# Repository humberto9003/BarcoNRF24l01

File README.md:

# Enlace con NRF24L01
Este repositorio contiene el programa para comunicar dos modulos NRF24L01, enviando las señales analogicas de un joystick por radiocomunicacion (2.4GHZ) para controlar un servomotor SG90 y un motor Brushless.

### Requisitos
Para que el código de este repositorio funcione, es necesario contar con lo siguiente:

- Arduino Uno
- IDE de Arduino 1.8 o superior
- Biblioteca RF24
- Servomotor SG90
- Motor Brushless A2212 Kv1400 / Kv2200
- NRF24L01
- Regulador de Voltaje para el NR24L01
- Modulo Joystick de dos ejes.

### Guías

Puedes obtener la biblioteca RF24 desde el siguiente enlace.

https://github.com/nRF24/RF24

Para conocer mas acerca del modulo NRF24L01 puede consultarlo en el siguiente enlace.

http://robots-argentina.com.ar/didactica/arduino-comunicacion-inalambrica-con-nrf24l01/

### Funcionamiento

Para observar el funcionamiento de este proyecto deberás realizar lo siguiente.

1. Configuarar los pines para el motor,servomotor y joystick de tu preferencia en el codigo de RX y Tx.
2. Si no cunetas con un NodeMCU se puede sustituir con otro arduino, solo tendrias que configuarar los pines de igual manera que el codigo de TX.
3. Alimentar el modulo NRF24L01 unicamete y exclusivamente con el regulador de  3.3V
4. En caso de usar el motor alimentarlo de una bateria externa y no del arduino ya que este no proporciona la corriente suficiente.

Podras comunicar dos arduinos por radiocomunicación, para este caso en particular poder manipular un servomor y motor con un Joystick. 

Por: [Humberto Pastor](https://https://github.com/humberto9003)

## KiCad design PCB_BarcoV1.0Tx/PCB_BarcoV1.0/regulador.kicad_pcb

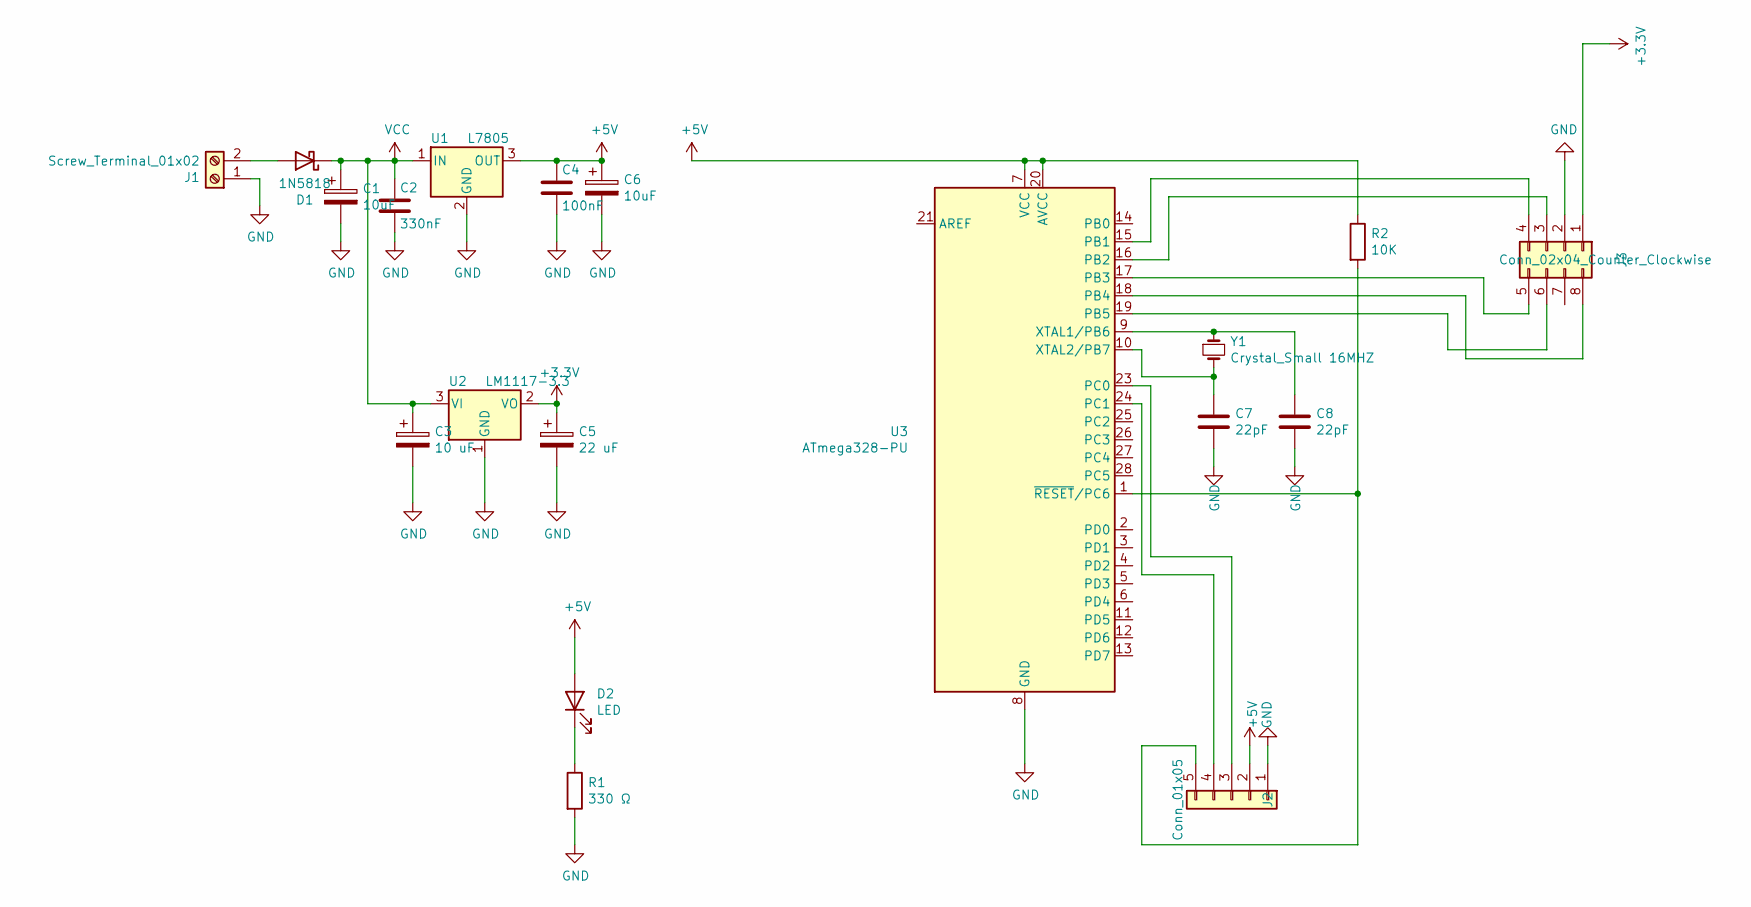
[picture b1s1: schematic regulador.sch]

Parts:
C1, C6: 10uF; CP_Radial_D5.0mm_P2.50mm
C2: 330nF; C_Disc_D6.0mm_W2.5mm_P5.00mm
C3: 10 uF; CP_Radial_D5.0mm_P2.50mm
C4: 100nF; C_Disc_D6.0mm_W2.5mm_P5.00mm
C5: 22 uF; CP_Radial_Tantal_D6.0mm_P2.50mm
C7, C8: 22pF; C_Disc_D5.0mm_W2.5mm_P2.50mm
D1: 1N5818; D_DO-41_SOD81_P10.16mm_Horizontal
D2: LED; LED_D5.0mm
J1: Screw_Terminal_01x02; TerminalBlock_Phoenix_PT-1,5-2-5.0-H_1x02_P5.00mm_Horizontal
J2: Conn_01x05; PinHeader_1x05_P2.54mm_Vertical
J3: Conn_02x04_Counter_Clockwise; PinSocket_2x04_P2.54mm_Vertical
R1: 330 Ω; R_Axial_DIN0207_L6.3mm_D2.5mm_P10.16mm_Horizontal
R2: 10K; R_Axial_DIN0207_L6.3mm_D2.5mm_P10.16mm_Horizontal
U1: L7805; TO-220-3_Horizontal_TabDown
U2: LM1117-3.3; TO-220-3_Horizontal_TabDown
U3: ATmega328-PU; DIP-28_W7.62mm_Socket_LongPads
Y1: Crystal_Small 16MHZ; Crystal_HC49-4H_Vertical

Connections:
+3V3: C5.1, J3.1, U2.2 (VO)
+5V: C4.1, C6.1, D2.2 (A), J2.2, R2.1, U1.3 (OUT), U3.7 (VCC), U3.20 (AVCC)
GND: C1.2, C2.2, C3.2, C4.2, C5.2, C6.2, C7.2, C8.2, J1.1, J2.1, J3.2, R1.2, U1.2 (GND), U2.1 (GND), U3.8 (GND), U3.22 (GND)
unnamed: C7.1, U3.10 (XTAL2/PB7), Y1.2
unnamed: C8.1, U3.9 (XTAL1/PB6), Y1.1
unnamed: D1.2 (A), J1.2
unnamed: D2.1 (K), R1.1
unnamed: J2.3, U3.23 (PC0)
unnamed: J2.4, U3.24 (PC1)
unnamed: J2.5, R2.2, U3.1 (~RESET~/PC6)
unnamed: J3.3, U3.16 (PB2)
unnamed: J3.4, U3.15 (PB1)
unnamed: J3.5, U3.17 (PB3)
unnamed: J3.6, U3.19 (PB5)
unnamed: J3.8, U3.18 (PB4)
VCC: C1.1, C2.1, C3.1, D1.1 (K), U1.1 (IN), U2.3 (VI)

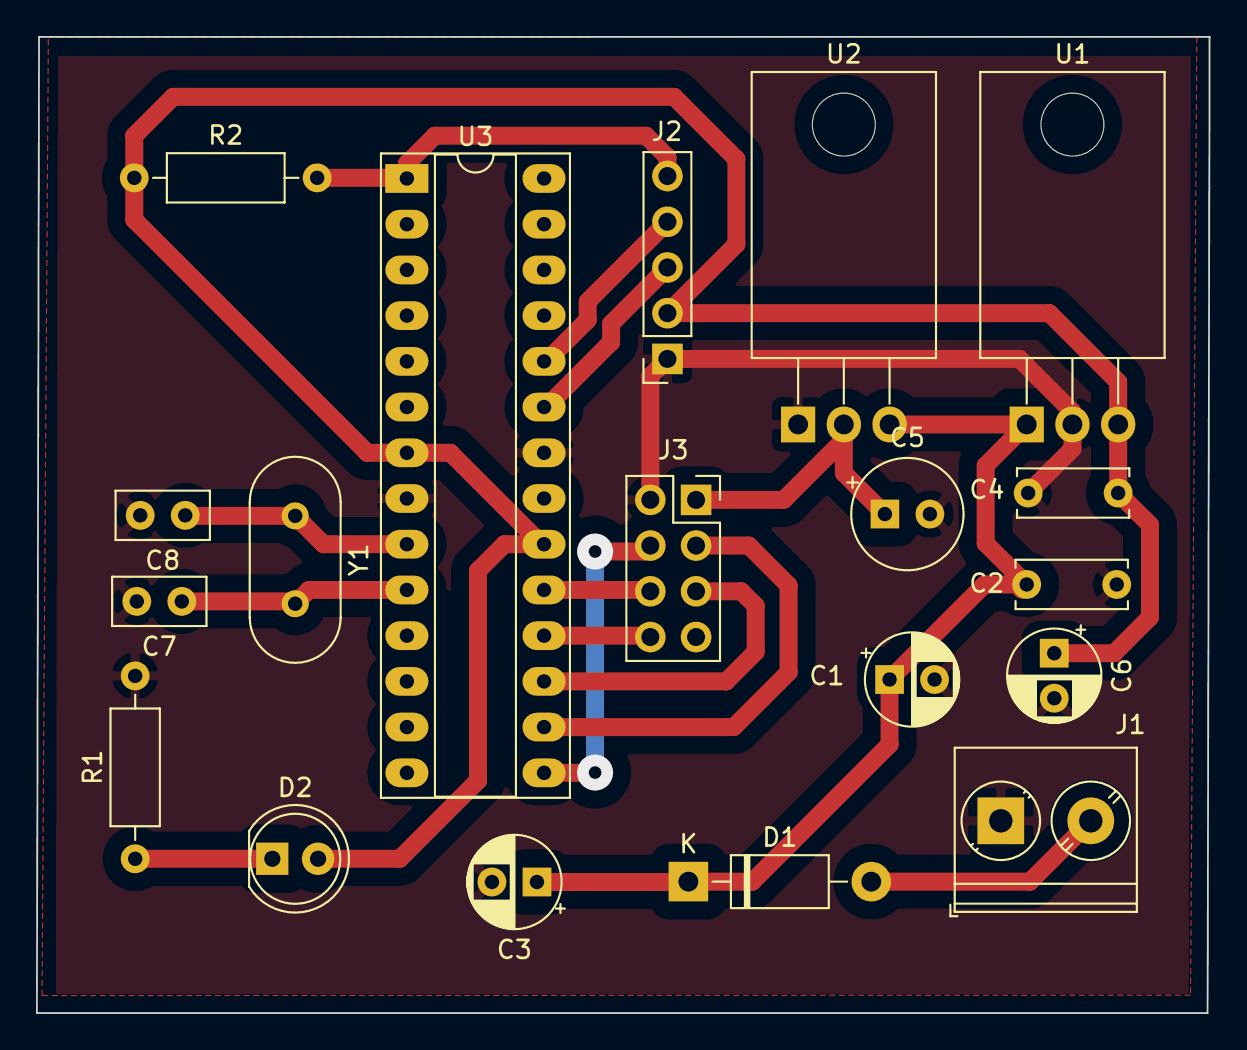
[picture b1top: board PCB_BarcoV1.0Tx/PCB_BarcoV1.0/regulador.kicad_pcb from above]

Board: 2 copper layers, 65.2 x 54.2 mm, 19 parts (0 on the bottom side), 16 nets.

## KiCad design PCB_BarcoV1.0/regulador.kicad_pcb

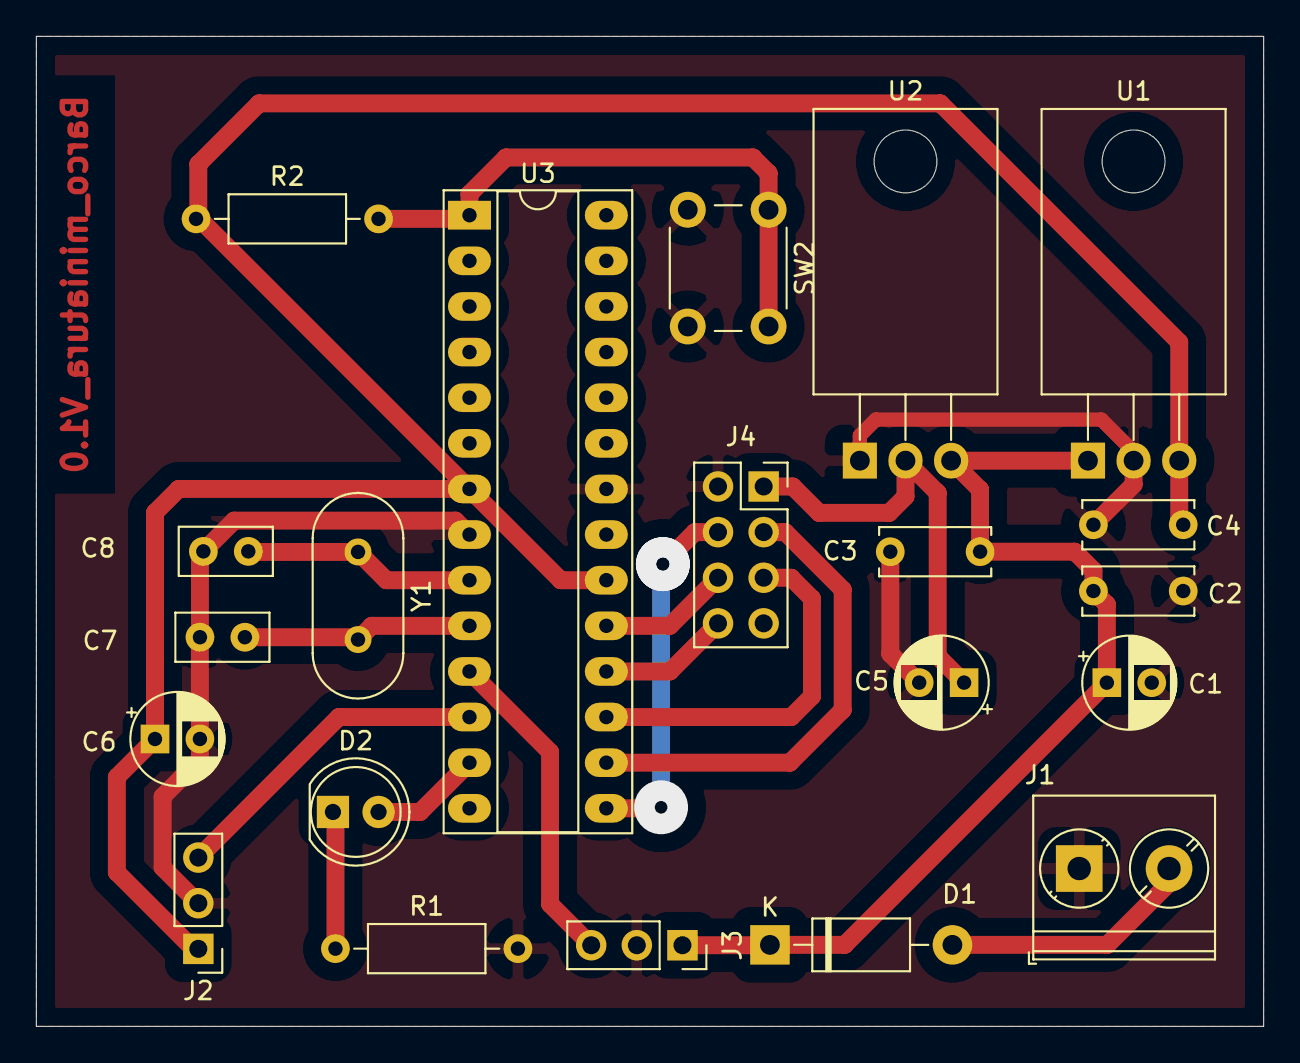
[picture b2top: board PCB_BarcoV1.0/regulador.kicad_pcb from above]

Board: 2 copper layers, 68.3 x 55.1 mm, 21 parts (0 on the bottom side), 17 nets.

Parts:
C1, C5, C6: 10uF; CP_Radial_D5.0mm_P2.50mm
C2: 330nF; C_Disc_D6.0mm_W2.5mm_P5.00mm
C3, C4: 100nF; C_Disc_D6.0mm_W2.5mm_P5.00mm
C7, C8: 22pF; C_Disc_D5.0mm_W2.5mm_P2.50mm
D1: 1N5818; D_DO-41_SOD81_P10.16mm_Horizontal
D2: LED; LED_D5.0mm
J1: Screw_Terminal_01x02; TerminalBlock_Phoenix_PT-1,5-2-5.0-H_1x02_P5.00mm_Horizontal
J2: Conn_01x03; PinHeader_1x03_P2.54mm_Vertical
J3: Conn_01x03; PinSocket_1x03_P2.54mm_Vertical
J4: Conn_02x04_Counter_Clockwise; PinSocket_2x04_P2.54mm_Vertical
R1: 330; R_Axial_DIN0207_L6.3mm_D2.5mm_P10.16mm_Horizontal
R2: 10K; R_Axial_DIN0207_L6.3mm_D2.5mm_P10.16mm_Horizontal
SW2: SW_Push; SW_PUSH_6mm_H5mm
U1: L7805; TO-220-3_Horizontal_TabDown
U2: LM1117-3.3; TO-220-3_Horizontal_TabDown
U3: ATmega328-PU; DIP-28_W7.62mm_Socket_LongPads
Y1: Crystal_Small 16MHZ; Crystal_HC49-4H_Vertical

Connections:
+3V3: C5.1, J4.1, U2.2
+5V: C4.1, C6.1, J2.1, R2.1, U1.3, U3.7, U3.20
GND: C1.2, C2.2, C3.2, C4.2, C5.2, C6.2, C7.2, C8.2, J1.1, J2.2, J3.2, J4.2, R1.2, SW2.2, U1.2, U2.1, U3.8, U3.22
unnamed: C7.1, U3.10, Y1.2
unnamed: C8.1, U3.9, Y1.1
unnamed: D1.2, J1.2
unnamed: D2.1, R1.1
unnamed: D2.2, U3.13
unnamed: J2.3, U3.12
unnamed: J3.3, U3.11
unnamed: J4.3, U3.16
unnamed: J4.4, U3.15
unnamed: J4.5, U3.17
unnamed: J4.6, U3.19
unnamed: J4.8, U3.18
unnamed: R2.2, SW2.1, U3.1
VCC: C1.1, C2.1, C3.1, D1.1, J3.1, U1.1, U2.3

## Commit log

2021-08-19 files of prototype of a radio frecuency ship
2021-08-19 delete image
    Corrigiendo nombre de imagen
2021-09-10 files add
